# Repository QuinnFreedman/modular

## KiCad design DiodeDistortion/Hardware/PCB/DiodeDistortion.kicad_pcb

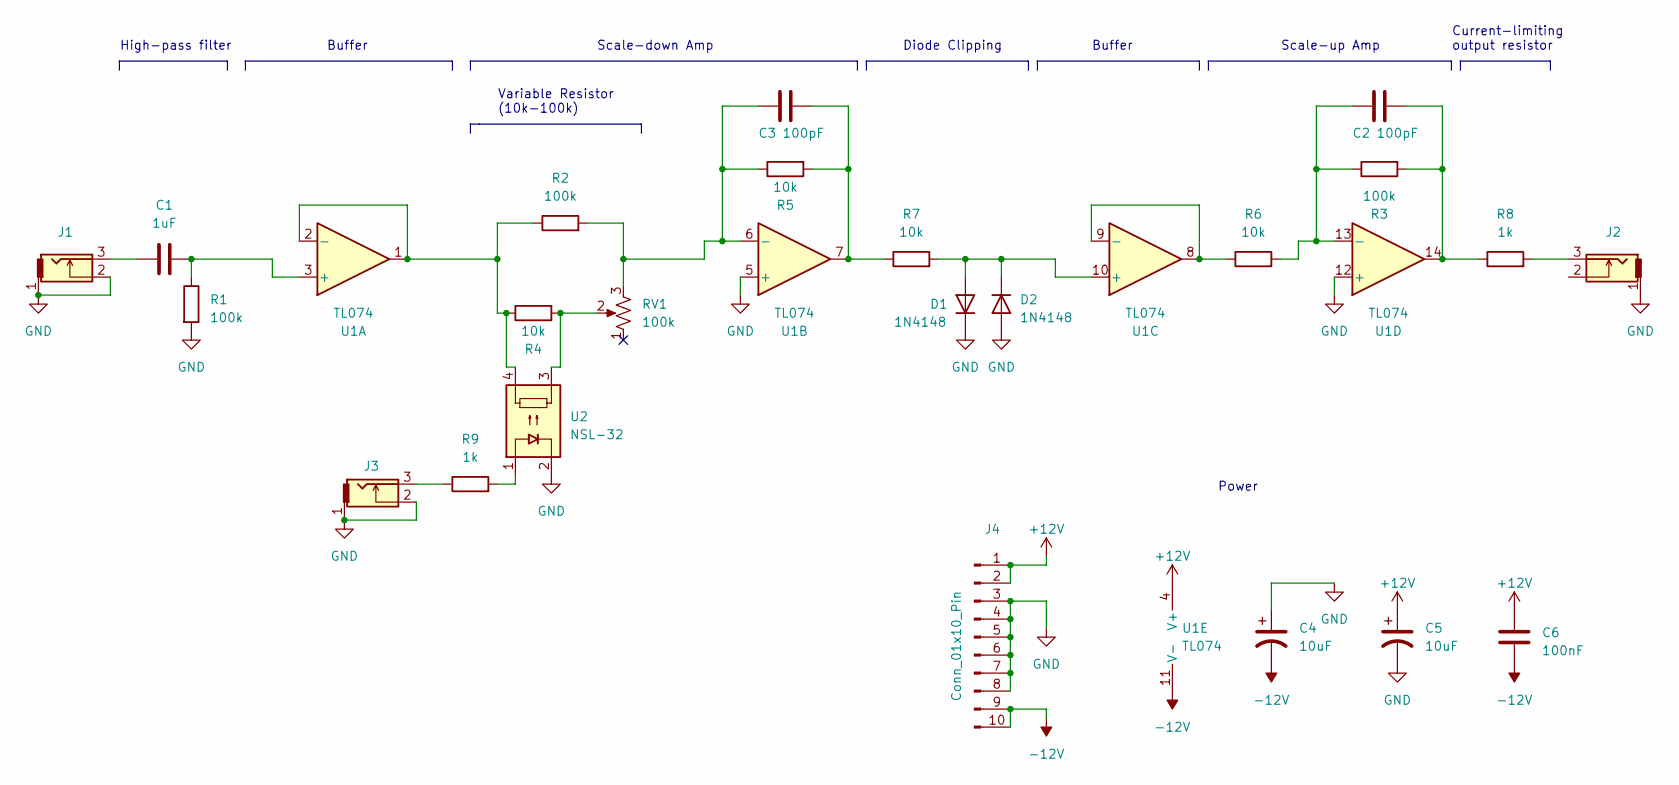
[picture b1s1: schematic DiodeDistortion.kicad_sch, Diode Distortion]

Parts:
C1: 1uF; C_Disc_D4.7mm_W2.5mm_P5.00mm
C2, C3: 100pF; C_Disc_D4.7mm_W2.5mm_P5.00mm
C4, C5: 10uF; CP_Radial_D4.0mm_P2.00mm
C6: 100nF; C_Disc_D4.7mm_W2.5mm_P5.00mm
D1, D2: 1N4148; D_DO-35_SOD27_P7.62mm_Horizontal
J1, J2, J3: THONKICONN
J4: Conn_01x10_Pin; PinSocket_2x05_P2.54mm_Vertical
R1, R2, R3: 100k; R_Axial_DIN0207_L6.3mm_D2.5mm_P7.62mm_Horizontal
R4, R5, R6, R7: 10k; R_Axial_DIN0207_L6.3mm_D2.5mm_P7.62mm_Horizontal
R8, R9: 1k; R_Axial_DIN0207_L6.3mm_D2.5mm_P7.62mm_Horizontal
RV1: 100k; Alpha_Potentiometer_Grounded
U1: TL074; DIP-14_W7.62mm
U2: NSL-32

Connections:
+12V: C5.1, C6.1, J4.1, J4.2, U1.4 (V+)
-12V: C4.2, C6.2, J4.9, J4.10, U1.11 (V-)
GND: C4.1, C5.2, D1.1 (K), D2.2 (A), J1.1, J1.2, J2.1, J3.1, J3.2, J4.3, J4.4, J4.5, J4.6, J4.7, J4.8, R1.2, RV1.MP, U1.5 (+), U1.12 (+), U2.2
unnamed: C1.1, J1.3
unnamed: C2.2, R3.2, R8.1, U1.14
unnamed: C3.2, R5.2, R7.1, U1.7
unnamed: D1.2 (A), D2.1 (K), R7.2, U1.10 (+)
unnamed: J2.3, R8.2
unnamed: J3.3, R9.1
unnamed: R4.2, RV1.2, U2.3
unnamed: R9.2, U2.1
unnamed: C1.2, R1.1, U1.3 (+)
unnamed: R2.1, R4.1, U1.1, U1.2 (-), U2.4
unnamed: C3.1, R2.2, R5.1, RV1.3, U1.6 (-)
unnamed: R6.1, U1.8, U1.9 (-)
unnamed: C2.1, R3.1, R6.2, U1.13 (-)

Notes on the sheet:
Buffer
High-pass filter
Variable Resistor (10k-100k)
Current-limiting output resistor
Scale-up Amp
Diode Clipping
Scale-down Amp
Power

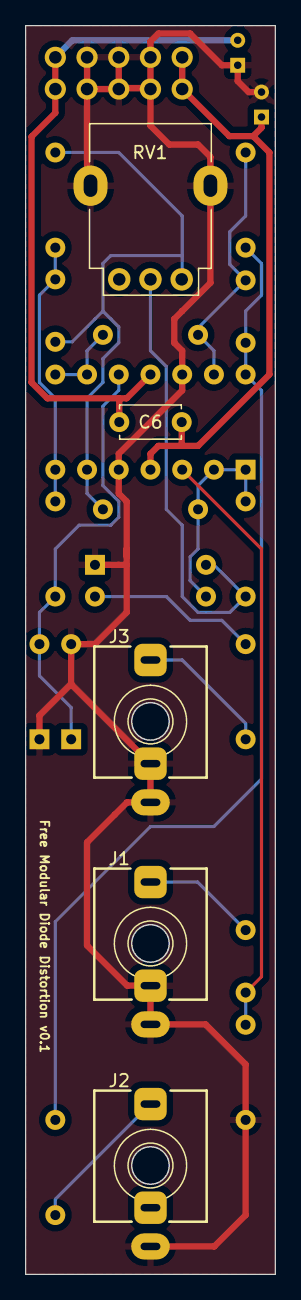
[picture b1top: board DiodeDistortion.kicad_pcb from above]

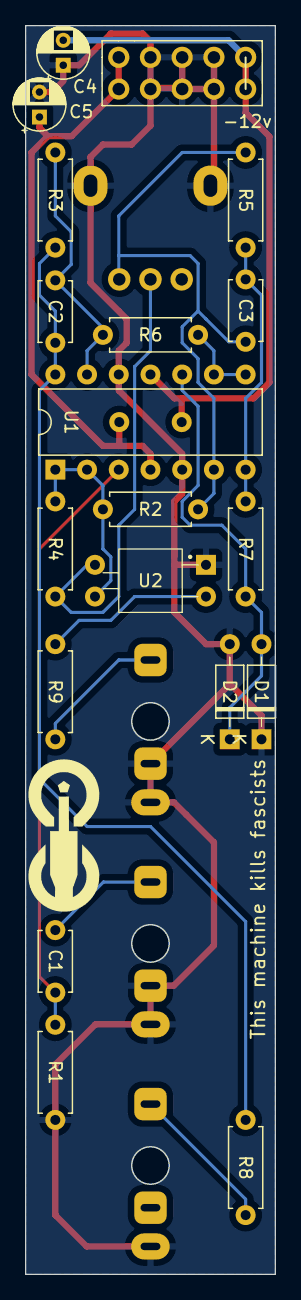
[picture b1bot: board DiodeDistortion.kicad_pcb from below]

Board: 2 copper layers, 20.0 x 100.0 mm, 24 parts (19 on the bottom side), 16 nets.

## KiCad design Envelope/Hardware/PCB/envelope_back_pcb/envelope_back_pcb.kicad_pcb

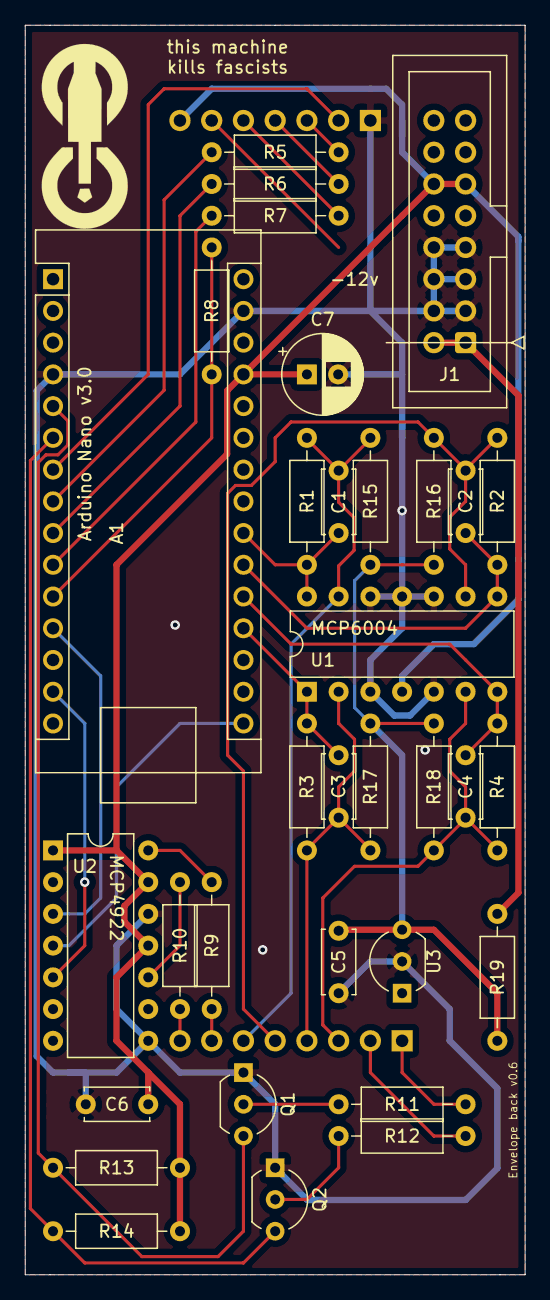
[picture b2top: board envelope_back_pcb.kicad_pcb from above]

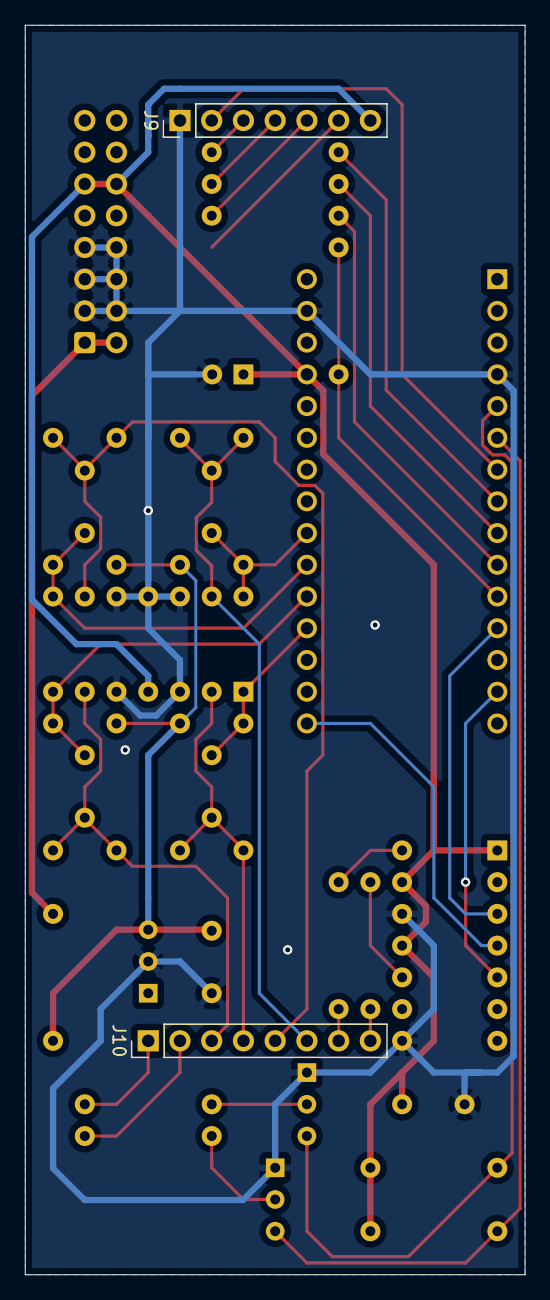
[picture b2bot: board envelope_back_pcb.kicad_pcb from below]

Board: 2 copper layers, 40.0 x 100.0 mm, 35 parts (2 on the bottom side), 35 nets.

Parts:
A1: Arduino_Nano_v3.x; Arduino_Nano
C1, C2, C3, C4: 10nF; C_Disc_D5.0mm_W2.5mm_P5.00mm
C5, C6: 100nF; C_Disc_D5.0mm_W2.5mm_P5.00mm
C7: 10uF; CP_Radial_D6.3mm_P2.50mm
J1: Conn_02x08_Odd_Even; IDC-Header_2x08_P2.54mm_Vertical
J9: Conn_01x07_Male; PinHeader_1x07_P2.54mm_Vertical
J10: Conn_01x08_Male; PinHeader_1x08_P2.54mm_Vertical
Q1, Q2: 2N3904; TO-92_Inline_Wide
R1, R2, R3, R4, R15, R16, R17, R18: 100kΩ; R_Axial_DIN0207_L6.3mm_D2.5mm_P10.16mm_Horizontal
R5, R6, R7, R8: 5.1kΩ; R_Axial_DIN0207_L6.3mm_D2.5mm_P10.16mm_Horizontal
R9, R10: 1kΩ; R_Axial_DIN0207_L6.3mm_D2.5mm_P10.16mm_Horizontal
R11, R12, R13, R14: 10kΩ; R_Axial_DIN0207_L6.3mm_D2.5mm_P10.16mm_Horizontal
R19: 470Ω; R_Axial_DIN0207_L6.3mm_D2.5mm_P10.16mm_Horizontal
U1: MCP6004; DIP-14_W7.62mm
U2: MCP4922; DIP-14_W7.62mm
U3: LM4040LP-5; TO-92_Inline_Wide

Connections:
+5V: A1.27, C6.1, C7.1, J1.11, J1.12, J9.7, R13.1, R14.1, U1.4, U2.1, U2.11, U2.13
+12V: J1.9, J1.10
-5v_REF: C5.2, R15.2, R16.2, R17.2, R18.2, R19.1, U3.3
-12V: J1.1, J1.2, R19.2
BUTTON: A1.7, J9.2
CV_1: C1.2, J10.6, R1.2, R15.1, U1.13
CV_1_5v: A1.22, C1.1, R1.1, U1.14
CV_2: C2.2, J10.5, R2.2, R16.1, U1.9
CV_2_5v: A1.21, C2.1, R2.1, U1.8
CV_3: C3.2, J10.4, R3.2, R17.1, U1.2
CV_3_5v: A1.19, C3.1, R3.1, U1.1
CV_4: C4.2, J10.3, R4.2, R18.1, U1.6
CV_4_5v: A1.20, C4.1, R4.1, U1.7
DAC_CS: A1.12, U2.3
GATE_IN: J10.1, R11.2
GATE_IN_5v: A1.5, Q1.3, R13.2
GND: A1.4, A1.29, C5.1, C6.2, C7.2, J1.3, J1.4, J1.5, J1.6, J1.7, J1.8, J9.1, Q1.1, Q2.1, U1.3, U1.5, U1.10, U1.11, U1.12, U2.8, U2.12, U3.2
LED_1: J9.3, R5.2
LED_2: J9.4, R6.2
LED_3: J9.5, R7.2
LED_4: J9.6, R8.2
unnamed: A1.8, R5.1
unnamed: A1.9, R6.1
unnamed: A1.10, R7.1
unnamed: A1.11, R8.1
unnamed: Q1.2, R11.1
unnamed: Q2.2, R12.1
unnamed: R9.2, U2.14
unnamed: R10.2, U2.10
OUT: J10.7, R9.1
OUT_INV: J10.8, R10.1
SPI_MOSI: A1.14, U2.5
SPI_SCK: A1.16, U2.4
TRIG_IN: J10.2, R12.2
TRIG_IN_5v: A1.6, Q2.3, R14.2

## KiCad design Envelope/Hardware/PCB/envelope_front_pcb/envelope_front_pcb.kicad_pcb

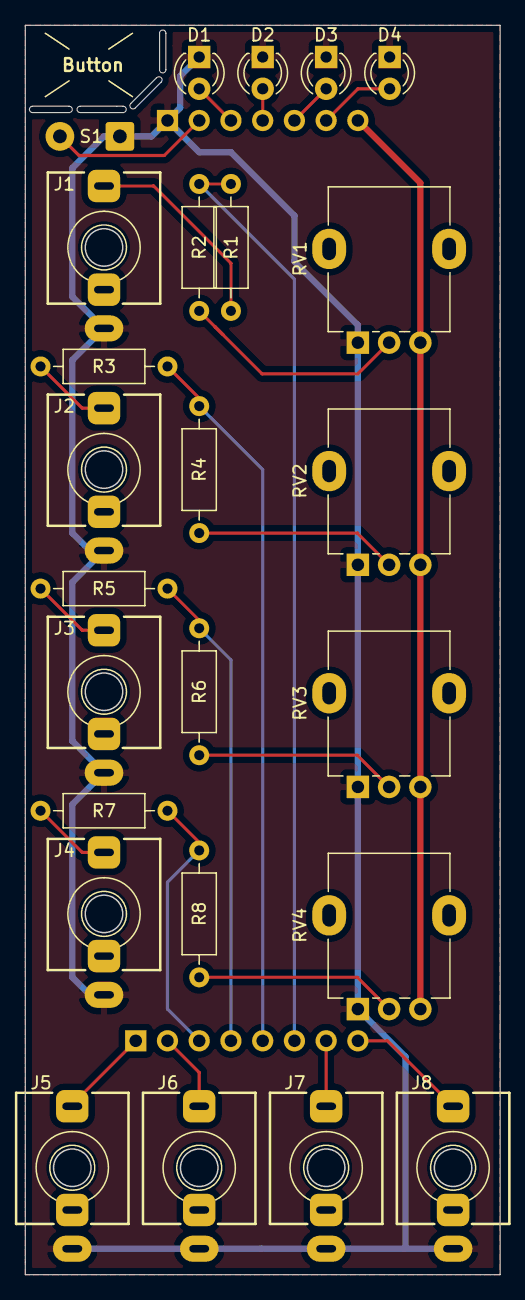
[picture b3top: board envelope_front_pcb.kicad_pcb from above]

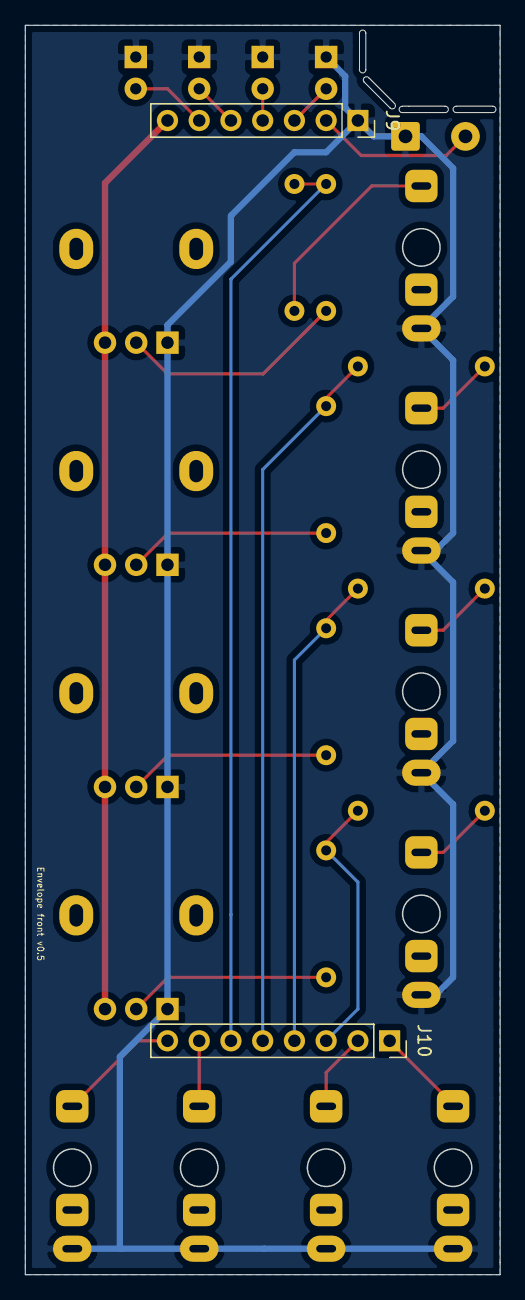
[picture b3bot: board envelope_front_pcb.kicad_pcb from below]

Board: 2 copper layers, 38.0 x 100.0 mm, 27 parts (2 on the bottom side), 23 nets.

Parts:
D1, D2, D3, D4: LED; LED_D3.0mm_Clear
J1, J2, J3, J4, J5, J6, J7, J8: THONKICONN
J9: Conn_01x07_Female; PinSocket_1x07_P2.54mm_Vertical
J10: Conn_01x08_Female; PinSocket_1x08_P2.54mm_Vertical
R1, R2, R3, R4, R5, R6, R7, R8: 100kΩ; R_Axial_DIN0207_L6.3mm_D2.5mm_P10.16mm_Horizontal
RV1, RV2, RV3, RV4: 10kΩ; Potentiometer_Alpha_RD901F-40-00D_Single_Vertical
S1: Conn_01x02_Female; SolderWire-0.5sqmm_1x02_P4.8mm_D0.9mm_OD2.3mm

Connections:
+5V: J9.7, RV1.3, RV2.3, RV3.3, RV4.3
BUTTON: J9.2, S1.2
CV_1: J10.6, R1.2, R2.1
CV_2: J10.5, R3.2, R4.1
CV_3: J10.4, R5.2, R6.1
CV_4: J10.3, R7.2, R8.1
GATE_IN: J5.3, J10.1
GND: D1.1, D2.1, D3.1, D4.1, J1.1, J2.1, J3.1, J4.1, J5.1, J6.1, J7.1, J8.1, J9.1, RV1.1, RV2.1, RV3.1, RV4.1, S1.1
LED_1: D1.2, J9.3
LED_2: D2.2, J9.4
LED_3: D3.2, J9.5
LED_4: D4.2, J9.6
unnamed: J1.3, R1.1
unnamed: J2.3, R3.1
unnamed: J3.3, R5.1
unnamed: J4.3, R7.1
unnamed: R2.2, RV1.2
unnamed: R4.2, RV2.2
unnamed: R6.2, RV3.2
unnamed: R8.2, RV4.2
OUT: J7.3, J10.7
OUT_INV: J8.3, J10.8
TRIG_IN: J6.3, J10.2

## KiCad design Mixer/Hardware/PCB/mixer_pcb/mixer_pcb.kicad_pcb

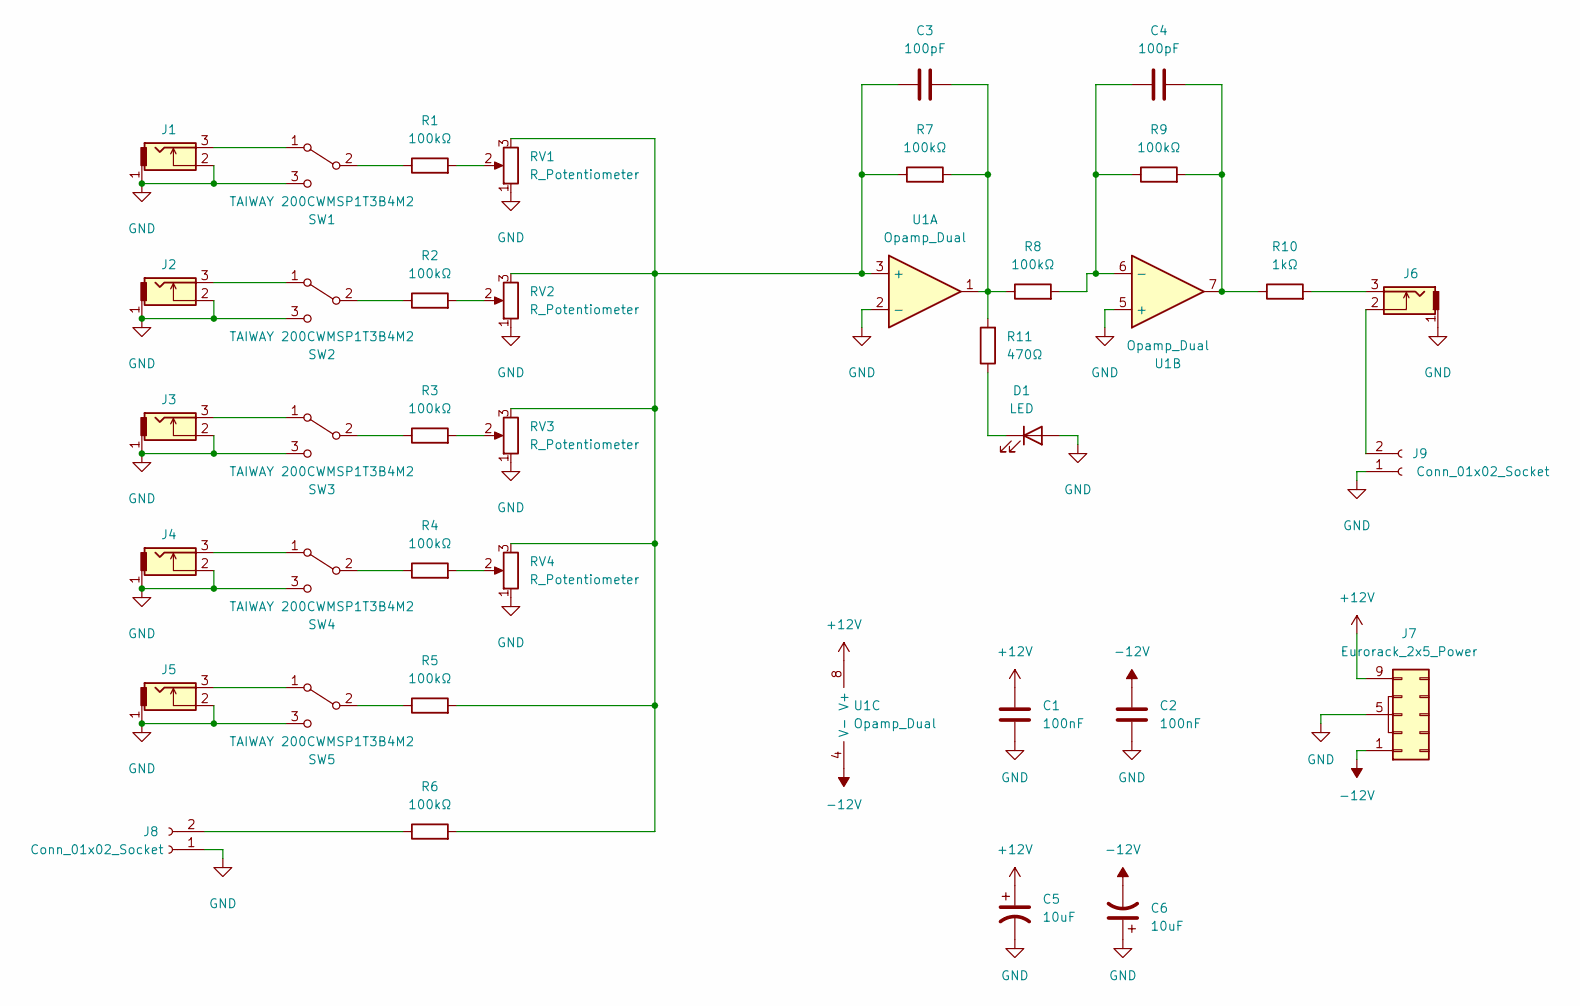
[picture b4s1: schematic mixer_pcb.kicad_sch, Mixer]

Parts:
C1, C2: 100nF; C_Disc_D4.7mm_W2.5mm_P5.00mm
C3, C4: 100pF; C_Disc_D4.7mm_W2.5mm_P5.00mm
C5, C6: 10uF; CP_Radial_D4.0mm_P2.00mm
D1: LED; LED_D3.0mm
J1, J2, J3, J4, J5, J6: THONKICONN
J7: Eurorack_2x5_Power; IDC-Header_2x05_P2.54mm_Vertical
J8, J9: Conn_01x02_Socket; PinHeader_1x02_P2.54mm_Vertical
R1, R2, R3, R4, R5, R6, R7, R8, R9: 100kΩ; R_Axial_DIN0207_L6.3mm_D2.5mm_P10.16mm_Horizontal
R10: 1kΩ; R_Axial_DIN0207_L6.3mm_D2.5mm_P10.16mm_Horizontal
R11: 470Ω; R_Axial_DIN0207_L6.3mm_D2.5mm_P10.16mm_Horizontal
RV1, RV2, RV3, RV4: R_Potentiometer; Alpha_Potentiometer_Grounded
SW1, SW2, SW3, SW4, SW5: TAIWAY 200CWMSP1T3B4M2
U1: Opamp_Dual; DIP-8_W7.62mm

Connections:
+12V: C1.1, C5.1, J7.9 (+12v), J7.10 (+12v), U1.8 (V+)
-12V: C2.1, C6.2, J7.1 (-12v), J7.2 (-12v), U1.4 (V-)
GND: C1.2, C2.2, C5.2, C6.1, D1.2 (A), J1.1, J1.2, J2.1, J2.2, J3.1, J3.2, J4.1, J4.2, J5.1, J5.2, J6.1, J7.3 (GND), J7.4 (GND), J7.5 (GND), J7.6 (GND), J7.7 (GND), J7.8 (GND), J8.1, J9.1, RV1.1, RV1.MP, RV2.1, RV2.MP, RV3.1, RV3.MP, RV4.1, RV4.MP, SW1.3 (C), SW2.3 (C), SW3.3 (C), SW4.3 (C), SW5.3 (C), U1.2 (-), U1.5 (+)
unnamed: C3.2, R7.2, R8.1, R11.2, U1.1
unnamed: C4.2, R9.2, R10.1, U1.7
unnamed: D1.1 (K), R11.1
unnamed: J6.3, R10.2
unnamed: J8.2, R6.1
unnamed: J6.2, J9.2
unnamed: R1.2, RV1.2
unnamed: R2.2, RV2.2
unnamed: R3.2, RV3.2
unnamed: R4.2, RV4.2
unnamed: J1.3, SW1.1 (A)
unnamed: R1.1, SW1.2 (B)
unnamed: J2.3, SW2.1 (A)
unnamed: R2.1, SW2.2 (B)
unnamed: J3.3, SW3.1 (A)
unnamed: R3.1, SW3.2 (B)
unnamed: J4.3, SW4.1 (A)
unnamed: R4.1, SW4.2 (B)
unnamed: J5.3, SW5.1 (A)
unnamed: R5.1, SW5.2 (B)
unnamed: C3.1, R5.2, R6.2, R7.1, RV1.3, RV2.3, RV3.3, RV4.3, U1.3 (+)
unnamed: C4.1, R8.2, R9.1, U1.6 (-)

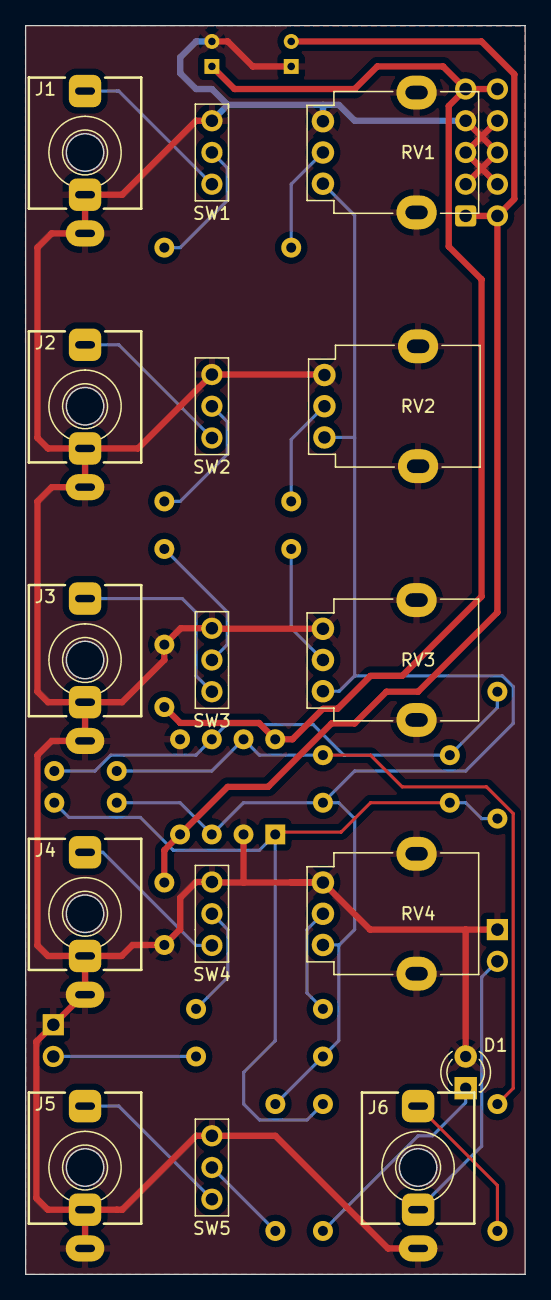
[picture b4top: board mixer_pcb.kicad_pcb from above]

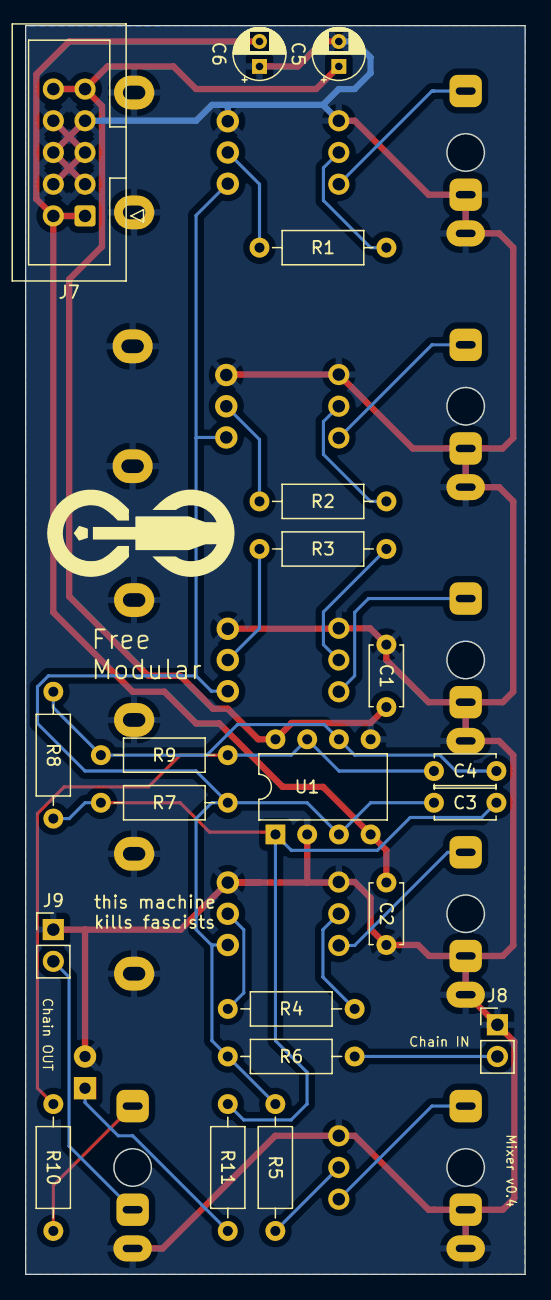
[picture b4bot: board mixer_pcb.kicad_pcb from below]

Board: 2 copper layers, 40.0 x 100.0 mm, 37 parts (21 on the bottom side), 25 nets.
